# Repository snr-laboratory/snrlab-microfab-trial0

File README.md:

# Trial run of micro-fabrication: interposer, individual FET, ACF, IC packaging

- Project planning documents go under [./doc/](./doc/ProjectPlans.md)
- Analysis, results, images, etc. go under [./analysis/](./analysis/)

## Software

### GDS creation/editing

- [KLayout](https://www.klayout.de/)
- [GDSFactory](https://gdsfactory.github.io/gdsfactory/)

### Documentation

- Recommend using <https://github.dev/> to directly open `.md` files on GitHub in browser (vscode in browser) to edit
- Use [draw.io](https://www.drawio.com/) for sketching.  `.md` can include and display the generated `.svg` files directly.  Install vscode extension `Draw.io Integration` to edit sketches in vscode directly.
- Clearly separate `.md` files and `assets` such as sketches and figures/images.  Put those under `./assets` directory.

### Python
  
- Create: `$(PYTHON) -m venv --symlinks --system-site-packages --clear $(PYVENV)`
- Upgrade: `$(PYTHON) -m venv --symlinks --system-site-packages --upgrade --upgrade-deps $(PYVENV)`

### Git

- `git clone --recurse-submodules`
- `git pull --recurse-submodules --all --rebase --prune && git gc --aggressive`

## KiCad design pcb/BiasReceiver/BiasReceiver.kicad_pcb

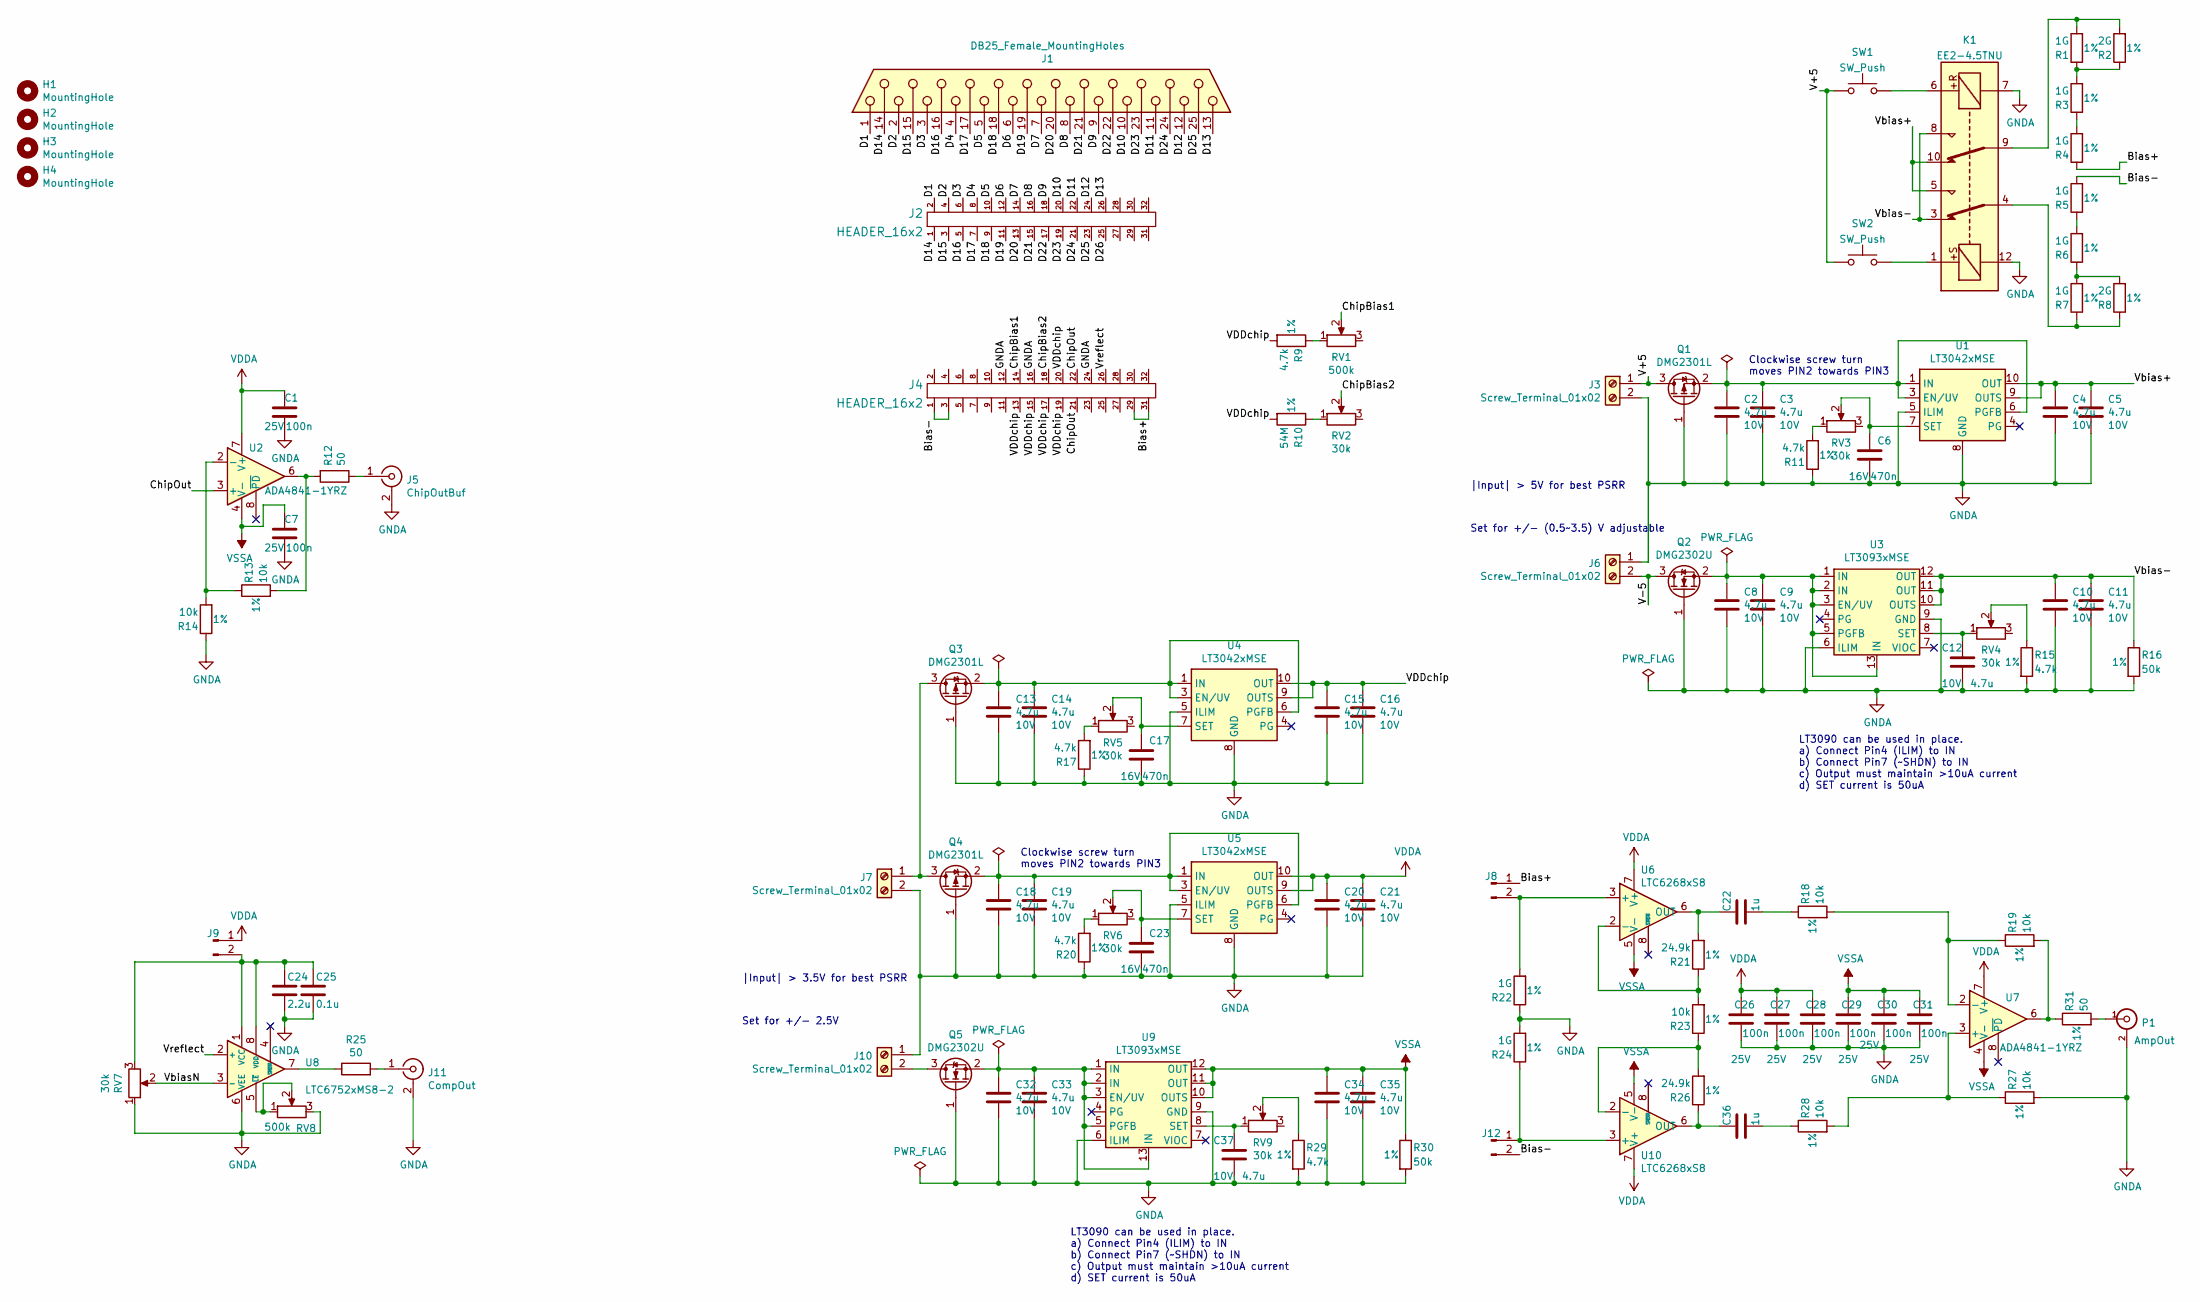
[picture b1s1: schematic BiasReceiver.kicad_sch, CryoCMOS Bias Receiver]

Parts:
C1, C7, C26, C27, C28, C29, C30, C31: 100n; C_0603_1608Metric
C2, C3, C4, C5, C8, C9, C10, C11, C12, C13, C14, C15, C16, C18, C19, C20, C21, C32, C33, C34, C35, C37: 4.7u; C_0603_1608Metric
C6, C17, C23: 470n; C_0603_1608Metric
C22, C36: 1u; C_0603_1608Metric
C24: 2.2u; C_0603_1608Metric
C25: 0.1u; C_0603_1608Metric
H1, H2, H3, H4: MountingHole; MountingHole_3.2mm_M3
J1: DB25_Female_MountingHoles; DSUB-25_Female_EdgeMount_P2.77mm
J2, J4: HEADER_16x2; PinHeader_2x16_P2.54mm_Vertical
J3, J6, J7, J10: Screw_Terminal_01x02; WJ15-3.81-90deg-2P
J5: ChipOutBuf; SMA_Amphenol_132134-16_Vertical
J8, J9, J12: Conn_01x02_Male; PinHeader_1x02_P2.54mm_Vertical
J11: CompOut; SMA_Amphenol_132134-16_Vertical
K1: EE2-4.5TNU; Relay_DPDT_Kemet_EE2_NU_DoubleCoil
P1: AmpOut; SMA_Amphenol_132134-16_Vertical
Q1, Q3, Q4: DMG2301L; SOT-23
Q2, Q5: DMG2302U; SOT-23
R1, R3, R4, R5, R6, R7, R22, R24: 1G; R_1206_3216Metric
R2, R8: 2G; R_2512_6332Metric
R9, R11, R15, R17, R20, R29: 4.7k; R_0603_1608Metric
R10: 54M; R_0603_1608Metric
R12, R25, R31: 50; R_0603_1608Metric
R13, R14, R18, R19, R23, R27, R28: 10k; R_0603_1608Metric
R16, R30: 50k; R_0603_1608Metric
R21, R26: 24.9k; R_0603_1608Metric
RV1, RV8: 500k; Potentiometer_Bourns_3296W_Vertical
RV2, RV3, RV4, RV5, RV6, RV7, RV9: 30k; Potentiometer_Bourns_3296W_Vertical
SW1, SW2: SW_Push; SW_Push_1P1T_NO_6x6mm_H9.5mm
U1, U4, U5: LT3042xMSE; MSOP-10-1EP_3x3mm_P0.5mm_EP1.68x1.88mm
U2, U7: ADA4841-1YRZ; SOIC-8_3.9x4.9mm_P1.27mm
U3, U9: LT3093xMSE; MSOP-12-1EP_3x4mm_P0.65mm_EP1.65x2.85mm
U6, U10: LTC6268xS8; SOIC-8_3.9x4.9mm_P1.27mm
U8: LTC6752xMS8-2; MSOP-8_3x3mm_P0.65mm

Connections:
/Bias+: J4.29, J4.31, J8.1, R4.1
/Bias-: J4.1, J4.3, J12.2, R5.2
/ChipBias1: J4.14, RV1.2
/ChipBias2: J4.18, RV2.2
/ChipOut: J4.21, J4.22, U2.3 (+)
/D1: J1.1, J2.2
/D2: J1.2, J2.4
/D3: J1.3, J2.6
/D4: J1.4, J2.8
/D5: J1.5, J2.10
/D6: J1.6, J2.12
/D7: J1.7, J2.14
/D8: J1.8, J2.16
/D9: J1.9, J2.18
/D10: J1.10, J2.20
/D11: J1.11, J2.22
/D12: J1.12, J2.24
/D13: J1.13, J2.26
/D14: J1.14, J2.1
/D15: J1.15, J2.3
/D16: J1.16, J2.5
/D17: J1.17, J2.7
/D18: J1.18, J2.9
/D19: J1.19, J2.11
/D20: J1.20, J2.13
/D21: J1.21, J2.15
/D22: J1.22, J2.17
/D23: J1.23, J2.19
/D24: J1.24, J2.21
/D25: J1.25, J2.23
/D26: J2.25
/V+5: J3.1, Q1.3 (D), SW1.1, SW2.1
/V-5: J6.2, Q2.3 (D)
/VDDchip: C15.1, C16.1, J4.13, J4.15, J4.17, J4.19, J4.20, R9.2, R10.2, U4.9 (OUTS), U4.10 (OUT)
/Vbias+: C4.1, C5.1, K1.5, K1.10, U1.9 (OUTS), U1.10 (OUT)
/Vbias-: C10.1, C11.1, K1.3, K1.8, R16.1, U3.10 (OUTS), U3.11 (OUT), U3.12 (OUT)
/VbiasN: RV7.2, U8.3 (-)
/Vreflect: J4.26, U8.2 (+)
GNDA: C1.2, C2.2, C3.2, C4.2, C5.2, C6.2, C7.2, C8.2, C9.2, C10.2, C11.2, C12.2, C13.2, C14.2, C15.2, C16.2, C17.2, C18.2, C19.2, C20.2, C21.2, C23.2, C24.2, C25.2, C26.2, C27.2, C28.2, C29.2, C30.2, C31.2, C32.2, C33.2, C34.2, C35.2, C37.2, J3.2, J4.12, J4.16, J4.24, J5.2 (Ext), J6.1, J7.2, J10.1, J11.2 (Ext), K1.7, K1.12, P1.2 (Ext), Q1.1 (G), Q2.1 (G), Q3.1 (G), Q4.1 (G), Q5.1 (G), R11.1, R14.1, R15.2, R16.2, R17.1, R20.1, R22.1, R24.2, R27.2, R29.2, R30.2, RV7.1, RV8.3, U1.5 (ILIM), U1.8 (GND), U1.11 (GND), U3.6 (ILIM), U3.9 (GND), U4.5 (ILIM), U4.8 (GND), U4.11 (GND), U5.5 (ILIM), U5.8 (GND), U5.11 (GND), U8.6 (VEE), U9.6 (ILIM), U9.9 (GND)
unnamed: C22.2, R18.1
unnamed: C36.2, R28.1
unnamed: J5.1 (In), R12.1
unnamed: J7.1, Q3.3 (D), Q4.3 (D)
unnamed: J8.2, R22.2, U6.3 (+)
unnamed: C24.1, C25.1, J9.2, RV7.3, U8.1 (VCC), U8.8 (VDD)
unnamed: J10.2, Q5.3 (D)
unnamed: J11.1 (In), R25.2
unnamed: J12.1, R24.1, U10.3 (+)
unnamed: K1.1, SW2.2
unnamed: K1.4, R7.1, R8.1
unnamed: K1.6, SW1.2
unnamed: K1.9, R1.2, R2.2
unnamed: P1.1 (In), R31.2
unnamed: C2.1, C3.1, Q1.2 (S), U1.1 (IN), U1.2 (IN), U1.3 (EN/UV), U1.6 (PGFB)
unnamed: C8.1, C9.1, Q2.2 (S), U3.1 (IN), U3.2 (IN), U3.3 (EN/UV), U3.5 (PGFB), U3.13 (IN)
unnamed: C13.1, C14.1, Q3.2 (S), U4.1 (IN), U4.2 (IN), U4.3 (EN/UV), U4.6 (PGFB)
unnamed: C18.1, C19.1, Q4.2 (S), U5.1 (IN), U5.2 (IN), U5.3 (EN/UV), U5.6 (PGFB)
unnamed: C32.1, C33.1, Q5.2 (S), U9.1 (IN), U9.2 (IN), U9.3 (EN/UV), U9.5 (PGFB), U9.13 (IN)
unnamed: R1.1, R2.1, R3.2
unnamed: R3.1, R4.2
unnamed: R5.1, R6.2
unnamed: R6.1, R7.2, R8.2
unnamed: R9.1, RV1.1
unnamed: R10.1, RV2.1
unnamed: R11.2, RV3.1
unnamed: R12.2, R13.2, U2.6
unnamed: R15.1, RV4.2
unnamed: R17.2, RV5.1
unnamed: R19.2, R31.1, U7.6
unnamed: R20.2, RV6.1
unnamed: R25.1, U8.7
unnamed: R29.1, RV9.2
unnamed: C6.1, RV3.2, U1.7 (SET)
unnamed: R13.1, R14.2, U2.2 (-)
unnamed: C12.1, RV4.1, U3.8 (SET)
unnamed: C17.1, RV5.2, U4.7 (SET)
unnamed: C23.1, RV6.2, U5.7 (SET)
unnamed: R21.1, R23.2, U6.2 (-)
unnamed: C22.1, R21.2, U6.6 (OUT)
unnamed: R27.1, R28.2, U7.3 (+)
unnamed: R18.2, R19.1, U7.2 (-)
unnamed: RV8.1, RV8.2, U8.5 (~LE)
unnamed: C37.1, RV9.1, U9.8 (SET)
unnamed: R23.1, R26.2, U10.2 (-)
unnamed: C36.1, R26.1, U10.6 (OUT)
VDDA: C1.1, C20.1, C21.1, C26.1, C27.1, C28.1, J9.1, U2.7 (V+), U5.9 (OUTS), U5.10 (OUT), U6.7 (V+), U7.7 (V+), U10.7 (V+)
VSSA: C7.1, C29.1, C30.1, C31.1, C34.1, C35.1, R30.1, U2.4 (V-), U6.5 (V-), U7.4 (V-), U9.10 (OUTS), U9.11 (OUT), U9.12 (OUT), U10.5 (V-)

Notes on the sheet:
Clockwise screw turn moves PIN2 towards PIN3
LT3090 can be used in place. a) Connect Pin4 (ILIM) to IN b) Connect Pin7 (~SHDN) to IN c) Output must maintain >10uA current d) SET current is 50uA
|Input| > 5V for best PSRR
Set for +/- (0.5~3.5) V adjustable
|Input| > 3.5V for best PSRR
Set for +/- 2.5V

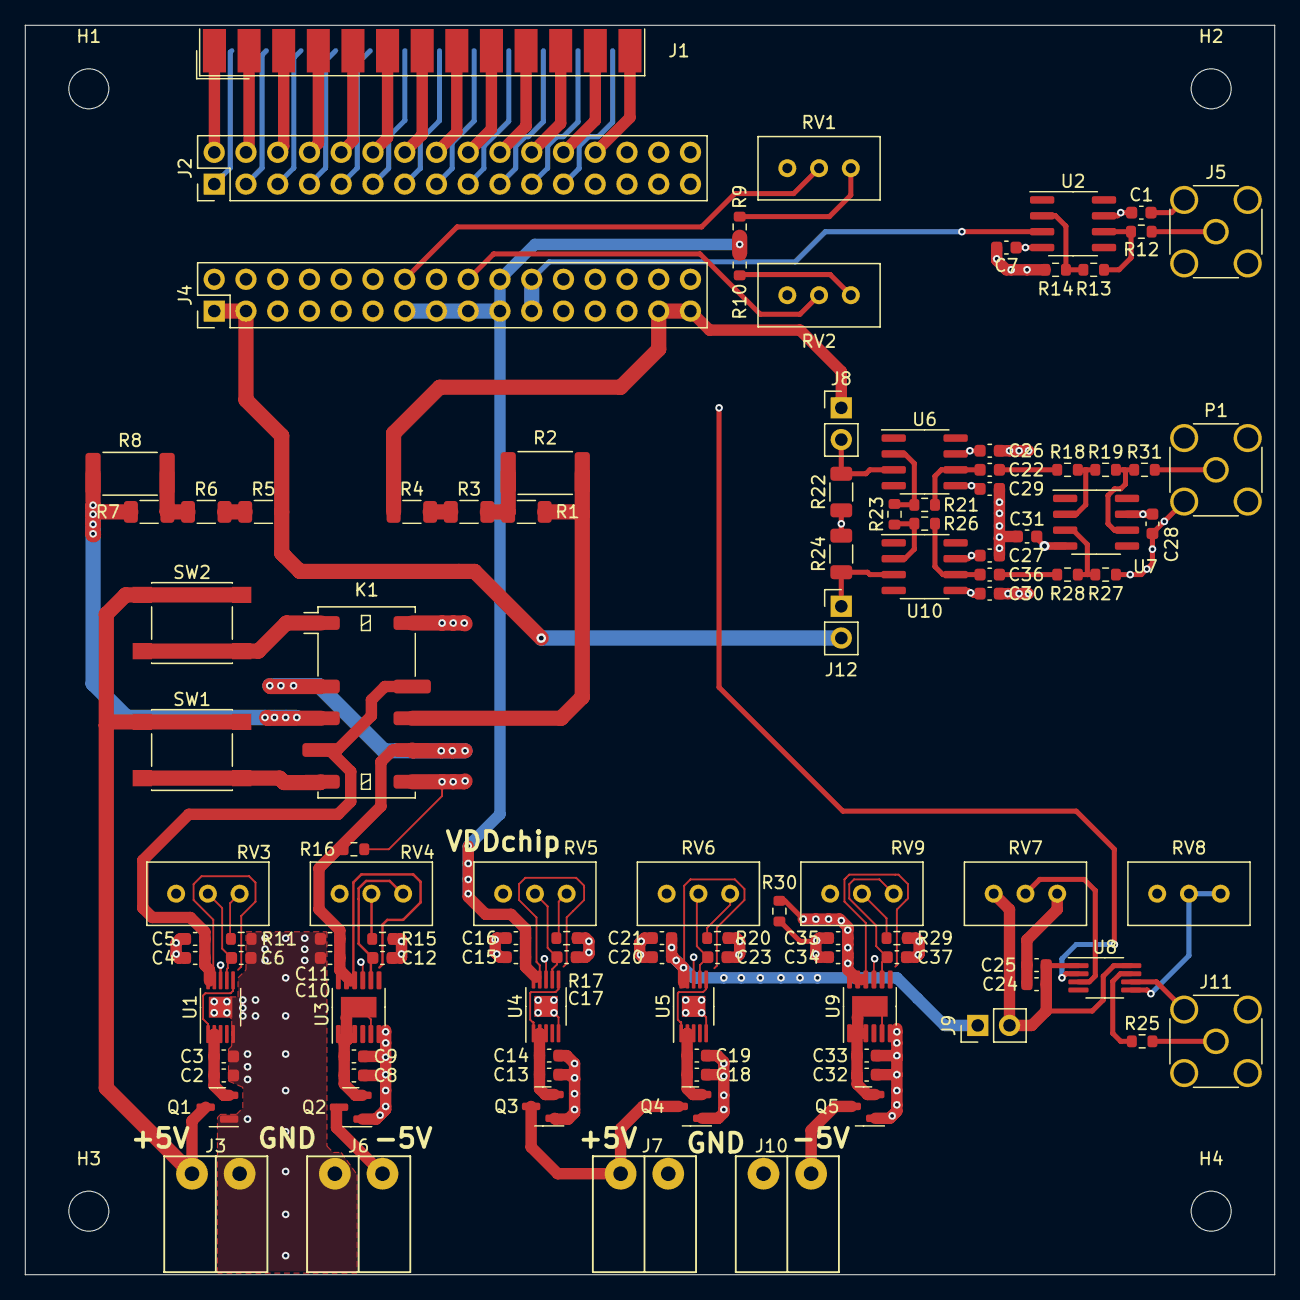
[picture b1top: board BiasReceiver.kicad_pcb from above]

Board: 4 copper layers, 99.9 x 99.9 mm, 112 parts (0 on the bottom side), 86 nets.

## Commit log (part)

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2025-08-13 Create resources
2025-10-06 Add dev_journal/g_task_deadline_2025_a.md
    Start progress tracking for Gumaro.
2025-10-15 Expand Journal with flyback diode and solenoid details
    Added detailed explanations about flyback diodes, current rise in solenoids, and wiring schematics for Arduino isolation.
2025-10-15 Replace image and document valve behavior changes
    Updated image reference and added new observations regarding the solenoid skinner valve behavior.
2025-10-15 Revise H2O ALD scope delay data and add images
    Updated delay measurements and added images for H2O ALD scope at different intervals.
2025-10-16 Add minimal test sketches for H2O and TMA ALD
2025-10-16 Add headings for actuation delay sections
2025-10-16 Add tasks for 20251016 analysis and measurements
    Added tasks for analyzing results and measuring delays.
2025-10-16 Update Journal.md with measurements and explanations
    Added inductive kickback measurement and details on relay signal behavior. Updated table headers and added explanations for rise time and actuation delay.
2025-10-16 Update Journal.md with kickback measurement details
    Added details about inductive kickback measurement and suggested improvements.
2025-10-21 Update Journal.md with new tasks and revisions
    Added new tasks for 20251020.21 and revised code section.
2025-10-22 Modify task identifier and add installation issue
    Updated task identifier and added a new item to the list.
2025-10-27 Resize images in Journal.md for improved presentation
    Updated images in Journal.md to use smaller dimensions for better layout.
2025-10-29 Add SV data collection images to Journal
2025-10-29 Document solenoid valve testing results and observations
    Added results of solenoid valve testing, including latency measurements and bounce duration observations.
2025-10-29 Fix date format and enhance task description
    Updated task details and corrected a typo in the date format.
2025-10-29 Fix typos and enhance clarity in tool operation section
    Corrected typos and improved clarity in the description of the tool operation and gas flow management.
2025-10-30 Revise Journal.md with new test code and procedures
    Updated the journal with new code outlines and test procedures for the dual-channel test and 3-valve sequence test.
2025-10-30 Clarify section title in Journal.md
    Updated the section title from 'New code outline' to 'New code rough outline' for clarity.
2025-10-31 Revise Journal.md with new diagram and updates
    Updated the journal with a new diagram and clarified issues with the new code.
2025-10-31 Document task resolution and settle time measurements
    Resolved coding issue and measured settle time between IN1 and IN4. Confirmed system behavior is reproducible and predictable with tight latencies.
2025-11-03 Add task for connecting IGC100 to PC
2025-11-03 Enhance timing tolerance section in electronic control system
    Added details about timing tolerance and its impact on film quality in the ALD process.
2025-11-03 Enhance electronic control system valves documentation
    Added a reference link and expanded on the importance of timing in ALD processes.
2025-11-04 Update dev_journal and ALD tasks.
2025-11-11 Add scope measurements section with images
    Added scope measurements and images for IN1 and IN2.
2025-11-11 Update performance metrics in gumaro_202511_a.md
    Added performance metrics for TMA ALD and H2O ALD.
2025-11-12 Add check valves section and update gas flow image
    Added check valves section with product link and updated gas flow image.
2025-11-12 Update IN3 and IN8 configurations in journal
    Added CH2 on +24V bus terminal and updated purge timings.
2025-11-12 Add images to K8 pulsing section in journal
    Added additional images to the K8 pulsing section.
2025-11-13 Task 20250926 complete. Add task 20251113.
2025-12-10 Add gas flow schematic to journal entry
    Added gas flow schematic images to the journal entry.
2026-01-16 Update dev_journal with new images and sections
    Added images for panel and gas flow schematic updates.
2026-01-16 Increase image dimensions in gas flow schematic
    Updated image sizes in gas flow schematic.
2026-03-17 Document ALD3 solenoid valve and oscilloscope results
    Added details about ALD3 electric solenoid valve and oscilloscope plots.
2026-03-17 Modify images and notes in ALD3 section
    Updated images in the ALD3 section with smaller dimensions and added notes on oscilloscope results.
2026-03-17 Refine formatting in gumaro_20251113_b.md
    Removed an empty line and adjusted formatting in the journal entry.
2026-03-17 Enhance dev journal with new observations and images
    Added additional images and observations for TMA and H2O pulse measurements. Updated notes on N2 and House main observations.
2026-03-28 Add new journal entry for ALD qmaterials
2026-03-28 Rename ALD_qmaterials_202603_a. to ALD_qmaterials_202603_a.md
2026-03-30 Rename ALD_Diamond_2026_a.md to ALD_Diamond_202603_a.md
2026-03-30 Simplify reactor description in project scope
    Removed specific mention of the SNR Lab tube reactor and simplified the description of the reactor setup while maintaining the context of the project.
2026-04-01 Add Vivo pump vacuum trials section to journal
2026-04-06 Update Lakeshore section with images and content
    Added images and updated content for Lakeshore section.
2026-04-07 Update dev_journal with new images and sections
    Added images and content related to Lakeshore and Vivo pump vacuum trials.
2026-04-25 Add Vivo chamber pump ultimate vac test section
    Added a new section for the Vivo chamber pump ultimate vacuum test with an image.
2026-04-25 Add image to Vivo chamber and pump vac test
    Added a new image to the Vivo chamber and pump section.
2026-04-30 Add pumpdown section and images to journal entry
2026-05-01 Update journal with new images and dates
    Added images and updated dates for pumpdown and real system tests.
2026-05-26 Document leak and e-stop issues in journal entry
    Added details about a leak and e-stop issues during run b.
2026-06-02 Update journal with dissertation and experiment details
    Added images and notes on dissertation proposal progress and experimental attempts.
2026-06-08 Update gas flow image in journal entry
    Added a new image for updated gas flow.
2026-06-17 Create Cu2O_validation_202606_a
2026-06-21 Rename Assembly 1.png to Assembly_1.png
2026-06-21 Rename samples A_K.png to samples_A_K.png
2026-06-21 Revise Cu2O validation metrics and add overlay image
    Updated reproducibility metrics and added new image.
2026-06-22 Add g_task_deadline_2025_a.md 20260622 task.
